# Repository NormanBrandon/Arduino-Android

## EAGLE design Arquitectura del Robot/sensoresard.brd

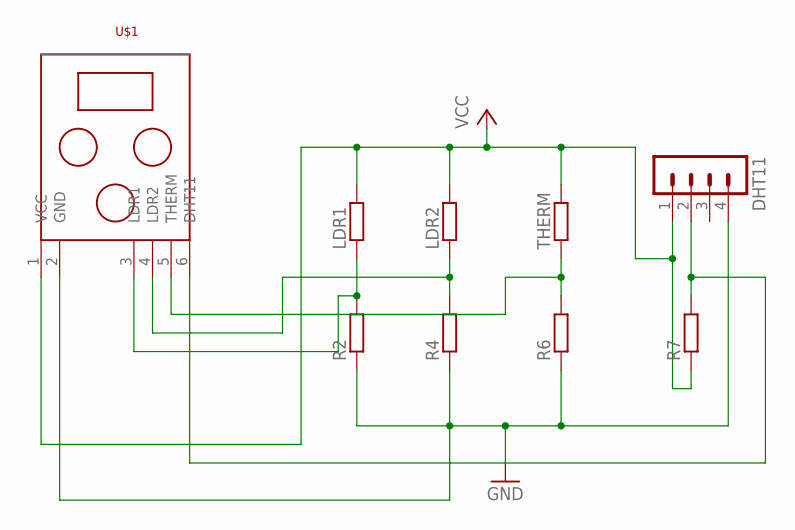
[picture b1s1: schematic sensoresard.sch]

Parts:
DHT11: MA04-1
LDR1, LDR2: R-EU_0204/7; 0204/7
R2, R4, R6, R7: R-EU_0204/7; 0204/7
THERM: R-EU_0204/7; 0204/7
U$1: PA

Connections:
GND: DHT11.4, R2.1, R4.1, R6.1, U$1.2 (GND)
unnamed: LDR1.1, R2.2, U$1.3 (LDR1)
unnamed: LDR2.1, R4.2, U$1.4 (LDR2)
unnamed: R6.2, THERM.1, U$1.5 (THERM)
unnamed: DHT11.2, R7.2, U$1.6 (DHT11)
VCC: DHT11.1, LDR1.2, LDR2.2, R7.1, THERM.2, U$1.1 (VCC)

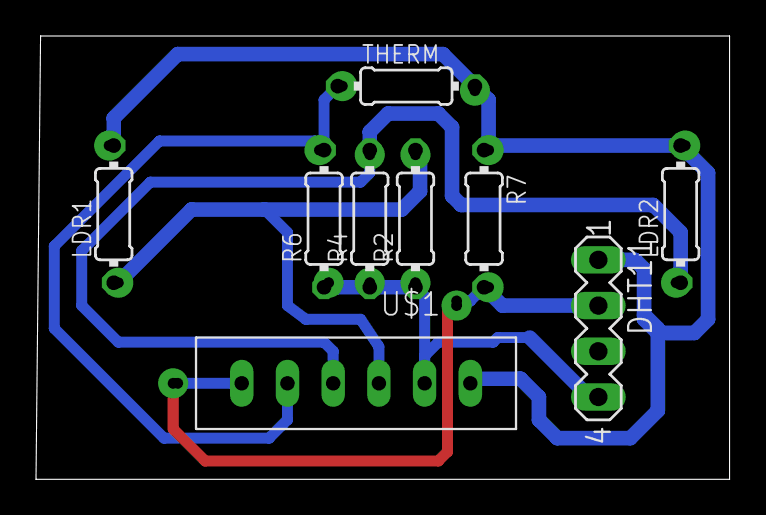
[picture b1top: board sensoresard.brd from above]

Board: 2 copper layers, 38.5 x 24.6 mm, 9 parts (0 on the bottom side), 6 nets.

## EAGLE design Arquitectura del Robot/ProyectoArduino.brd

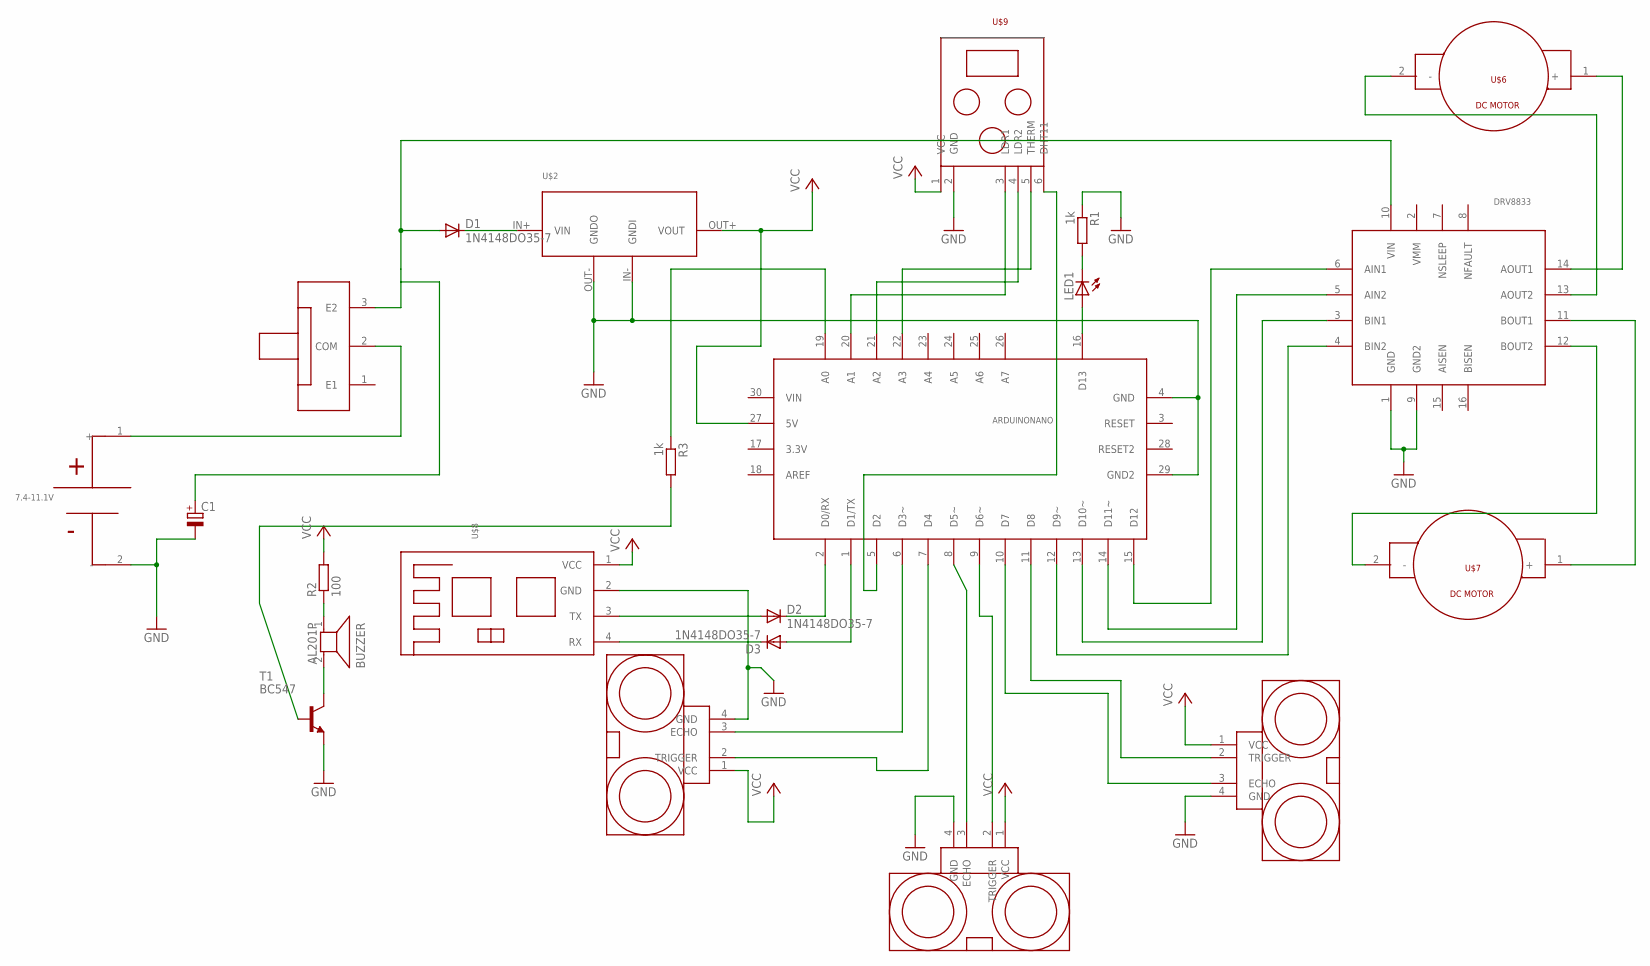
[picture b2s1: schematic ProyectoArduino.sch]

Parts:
7.4-11.1V: INBAT
ARDUINONANO: NANO
BUZZER: AL201P
C1: CPOL-EUE3.5-10; E3,5-10
D1, D2, D3: 1N4148DO35-7; DO35-7
DRV8833: MODULO
LED1: LED3MM
R1, R3: 1k; 0204/7
R2: 100; 0204/7
T1: BC547; TO92
U$1: TRIPLEPOLO
U$2: STEPDOWN
U$3, U$4, U$5: HC-SR04
U$6, U$7: OUTPUTMALE; OUPUTMALE
U$8: HC-06
U$9: PA

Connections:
GND: 7.4-11.1V.2 (-), ARDUINONANO.4 (GND), ARDUINONANO.29 (GND2), C1.-, DRV8833.1 (GND), DRV8833.9 (GND2), R1.1, T1.1 (E), U$2.IN- (GNDI), U$2.OUT- (GNDO), U$3.4 (GND), U$4.4 (GND), U$5.4 (GND), U$8.2 (GND), U$9.2 (GND)
unnamed: DRV8833.11 (BOUT1), U$7.1 (+)
unnamed: BUZZER.1, R2.1
unnamed: D1.C, U$2.IN+ (VIN)
unnamed: DRV8833.12 (BOUT2), U$7.2 (-)
unnamed: DRV8833.14 (AOUT1), U$6.1 (+)
unnamed: DRV8833.13 (AOUT2), U$6.2 (-)
unnamed: BUZZER.2, T1.3 (C)
unnamed: ARDUINONANO.15 (D12), DRV8833.6 (AIN1)
unnamed: ARDUINONANO.14 (D11~), DRV8833.5 (AIN2)
unnamed: ARDUINONANO.13 (D10~), DRV8833.3 (BIN1)
unnamed: ARDUINONANO.12 (D9~), DRV8833.4 (BIN2)
unnamed: C1.+, D1.A, DRV8833.10 (VIN), U$1.3 (E2)
unnamed: ARDUINONANO.19 (A0), R3.1
unnamed: D2.A, U$8.3 (TX)
unnamed: 7.4-11.1V.1 (+), U$1.2 (COM)
unnamed: ARDUINONANO.11 (D8), U$4.2 (TRIGGER)
unnamed: ARDUINONANO.10 (D7), U$4.3 (ECHO)
unnamed: ARDUINONANO.9 (D6~), U$5.2 (TRIGGER)
unnamed: ARDUINONANO.8 (D5~), U$5.3 (ECHO)
unnamed: ARDUINONANO.6 (D3~), U$3.3 (ECHO)
unnamed: ARDUINONANO.7 (D4), U$3.2 (TRIGGER)
unnamed: D3.C, U$8.4 (RX)
unnamed: R3.2, T1.2 (B)
unnamed: ARDUINONANO.1 (D1/TX), D3.A
unnamed: ARDUINONANO.2 (D0/RX), D2.C
unnamed: ARDUINONANO.20 (A1), U$9.3 (LDR1)
unnamed: ARDUINONANO.21 (A2), U$9.4 (LDR2)
unnamed: ARDUINONANO.22 (A3), U$9.5 (THERM)
unnamed: ARDUINONANO.5 (D2), U$9.6 (DHT11)
unnamed: ARDUINONANO.16 (D13), LED1.A
unnamed: LED1.K (C), R1.2
VCC: ARDUINONANO.27 (5V), R2.2, U$2.OUT+ (VOUT), U$3.1 (VCC), U$4.1 (VCC), U$5.1 (VCC), U$8.1 (VCC), U$9.1 (VCC)

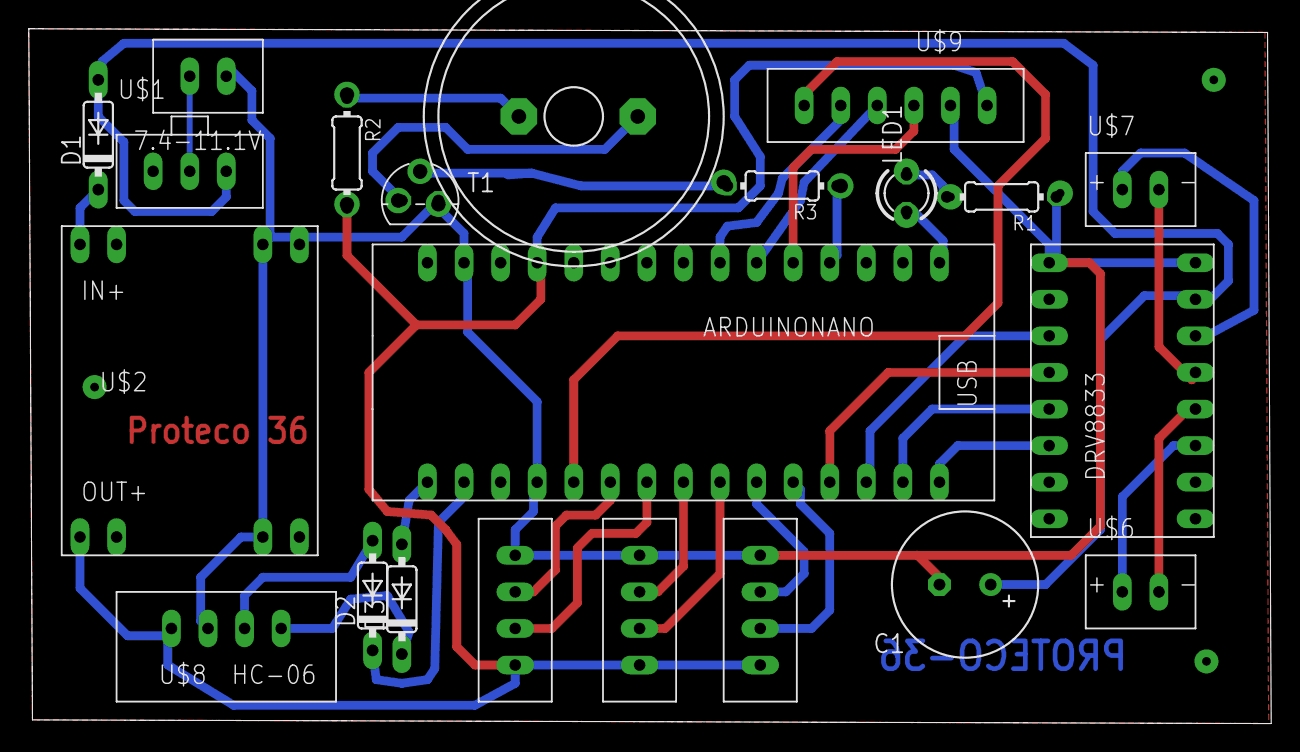
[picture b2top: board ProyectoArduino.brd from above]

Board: 2 copper layers, 86.3 x 48.2 mm, 22 parts (0 on the bottom side), 33 nets.

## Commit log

2018-06-03 Subiendo Hadware
2018-06-04 Pruebas de Ahdware con arduino
2018-06-05 la carpeta Proyecto_Arduino contiene la interfaz de la aplicacion de android
2018-06-06 falta background de botones y funcionalidades bt
2018-06-07 Conectando dispositivos bluetooth
2018-06-08 Conexion y envio existosos
2018-06-08 Programa d prueba para la aplicacion
2018-06-08 Programa d prueba para la aplicacion 21
2018-06-08 robot v1
2018-06-08 fusion jaaaa
2018-06-09 Mejorado
2018-06-09 bug fix
2018-06-09 bug fix2
2018-06-09 correccion datos
2018-06-09 Flechas persistentes
2018-06-09 normalizado
2018-06-09 algunos botones arrelados
2018-06-09 acelerometro funtions
2018-06-09 Otro push
2018-06-10 Letura de sensores
2018-06-10 heil Norman, bugfix
2018-06-11 control de robot bb con arduino, recepcion y conexion con app
2019-05-29 cambio inutil
